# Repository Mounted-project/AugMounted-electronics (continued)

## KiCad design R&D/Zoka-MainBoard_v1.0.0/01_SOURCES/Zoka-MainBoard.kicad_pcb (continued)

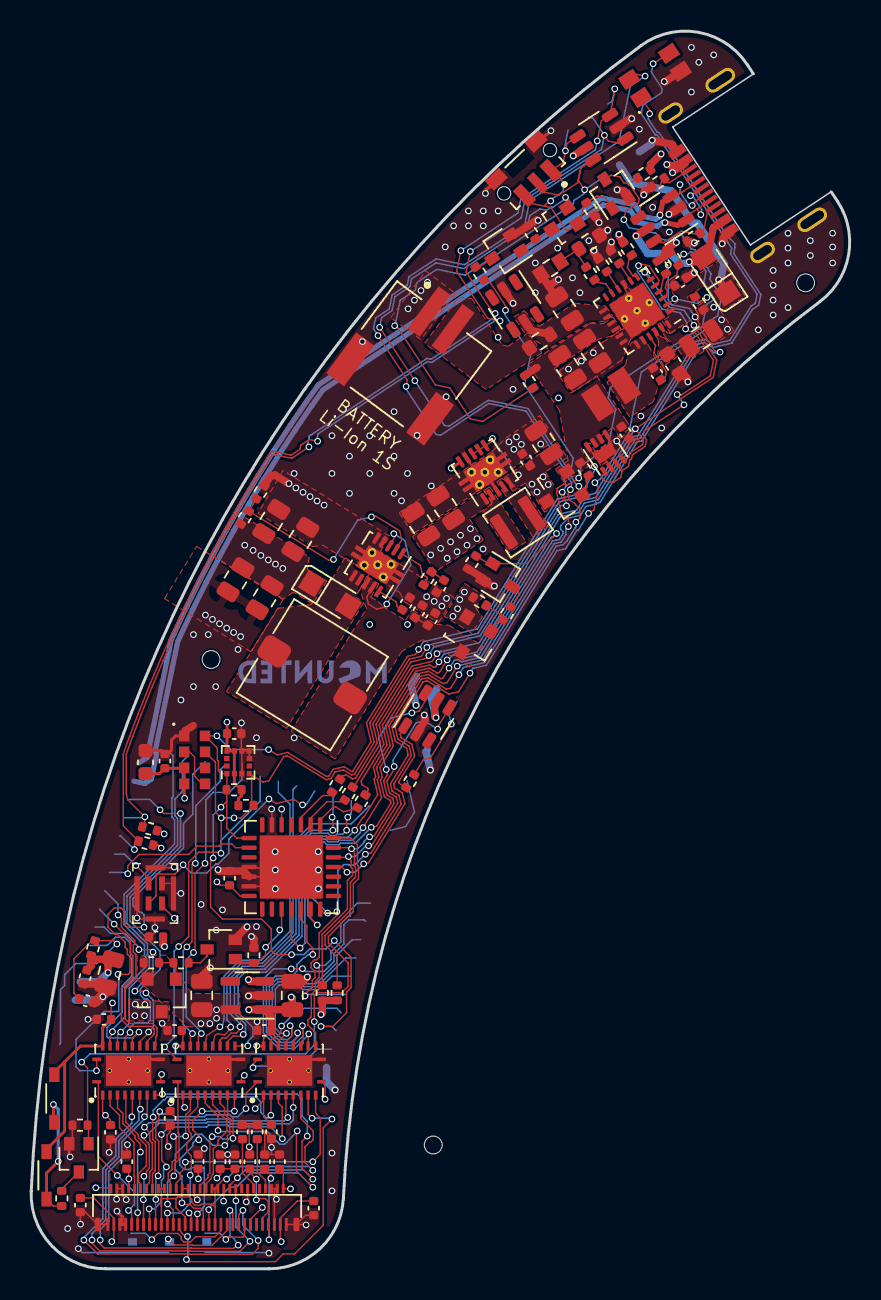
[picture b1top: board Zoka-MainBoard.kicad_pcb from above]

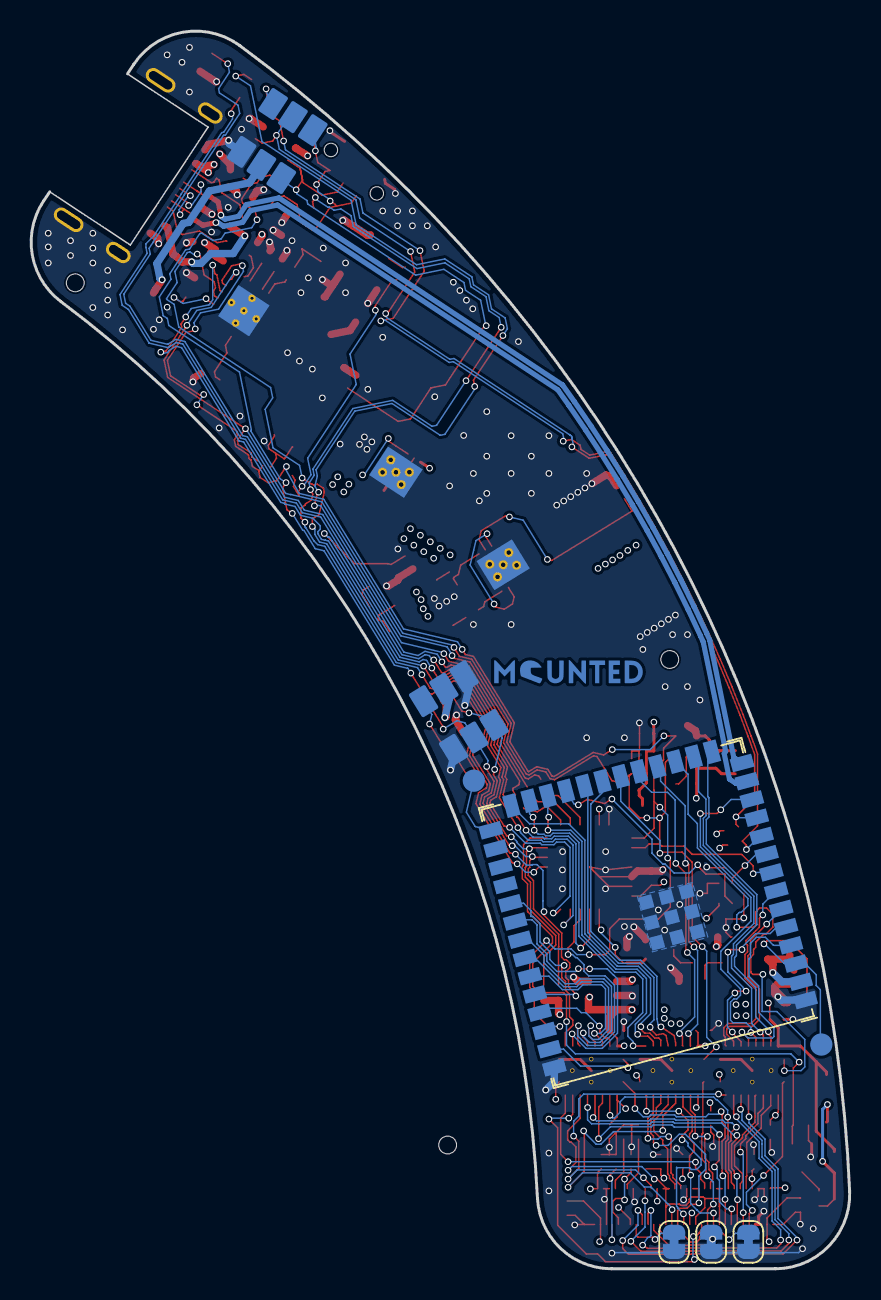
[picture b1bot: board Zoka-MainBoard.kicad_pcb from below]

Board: 4 copper layers, 55.1 x 83.3 mm, 136 parts (9 on the bottom side), 126 nets.

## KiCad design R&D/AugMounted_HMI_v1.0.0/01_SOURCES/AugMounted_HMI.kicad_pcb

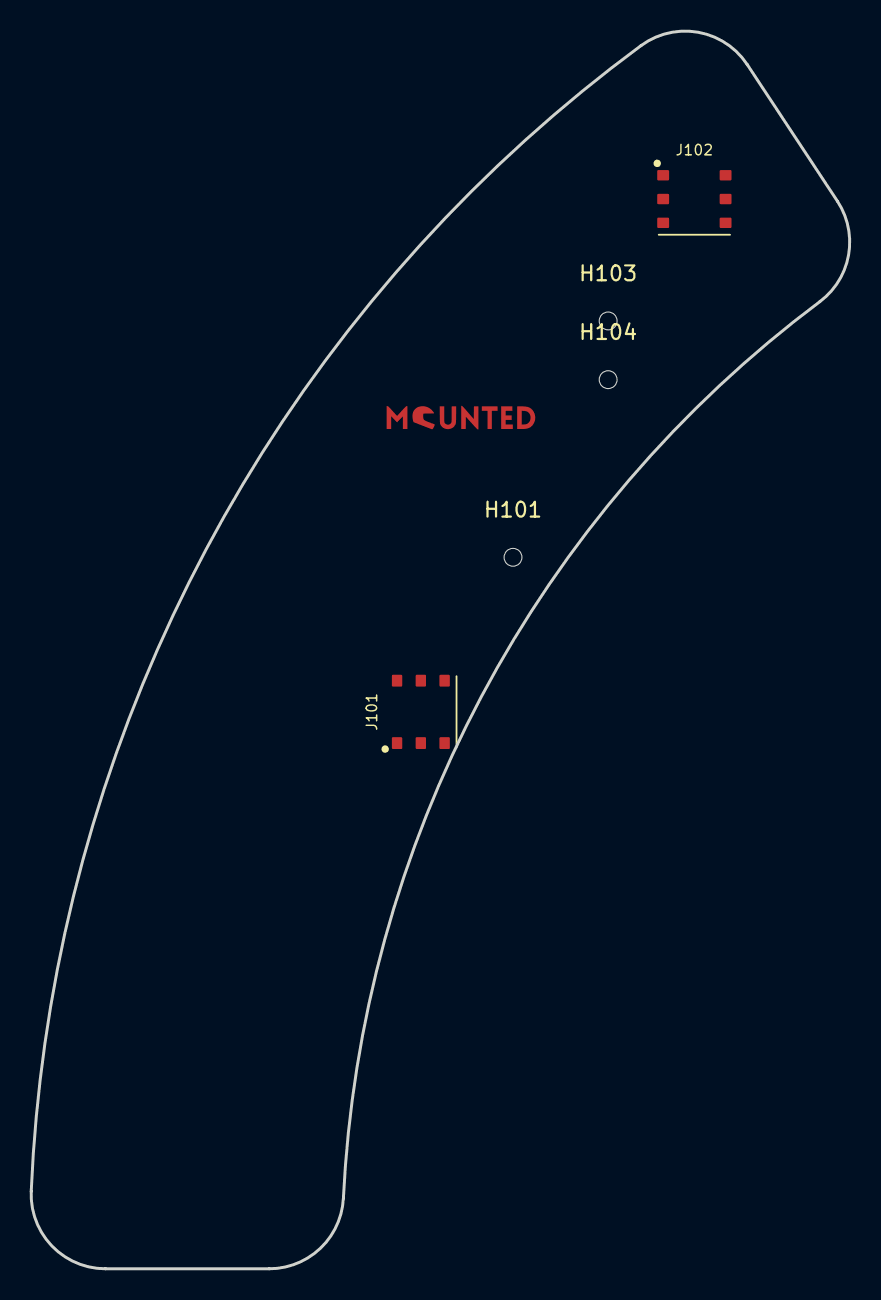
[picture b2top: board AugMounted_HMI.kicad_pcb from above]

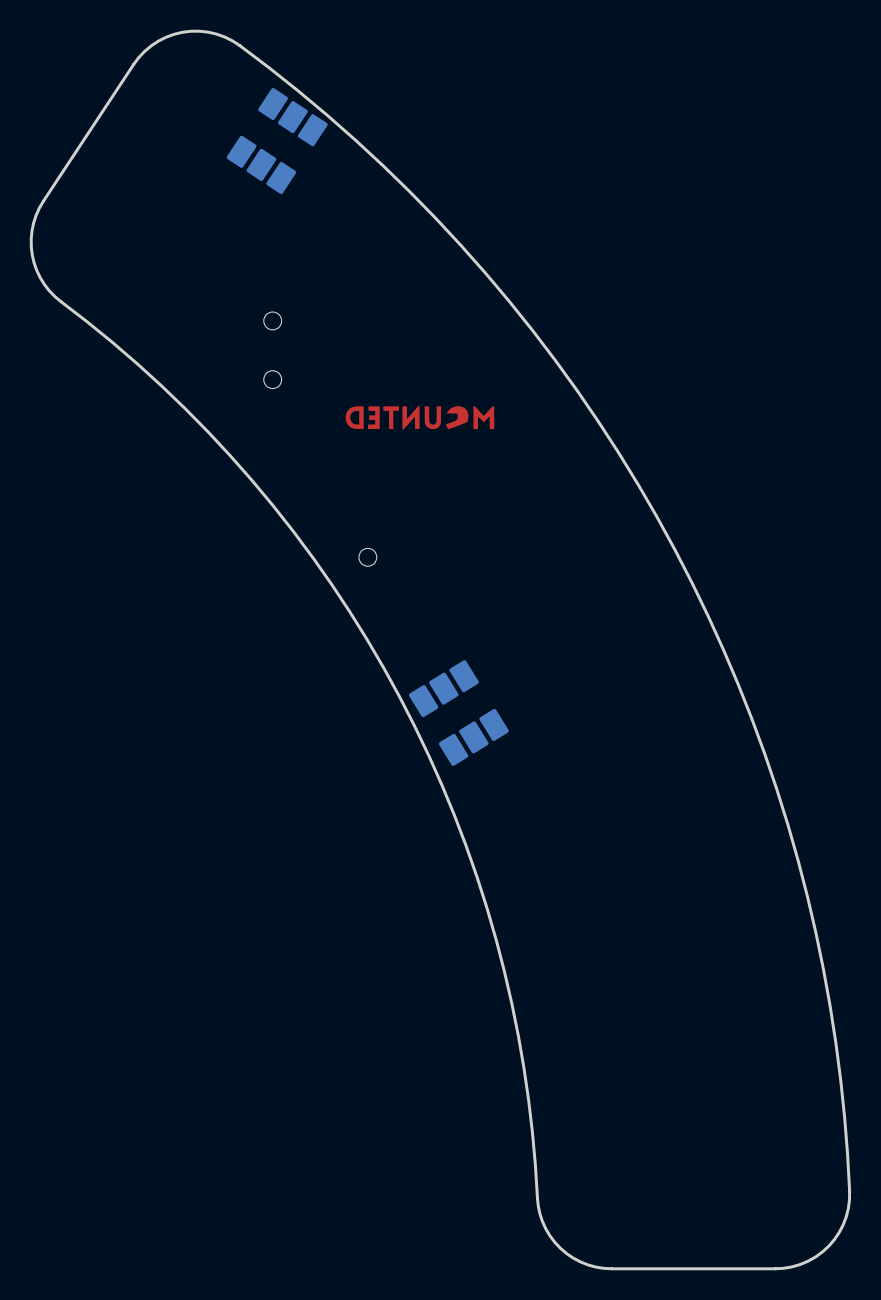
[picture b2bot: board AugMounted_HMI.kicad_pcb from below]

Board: 4 copper layers, 55.1 x 83.3 mm, 8 parts (2 on the bottom side), 3 nets, no tracks yet.

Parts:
H101, H103, H104: H_MOUNTING_HOLE_M1; MountingHole_1.2mm_M1
J101, J102: J_0788641001; J_788641001
J501, J504: J_0788641001_PAD; J_788641001_PAD
LOGO101: mounted_logo

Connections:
/GND_HMI_BOARD: J101.3, J102.3
GND: J501.3, J501.6, J504.3
unnamed: J101.1, J101.6

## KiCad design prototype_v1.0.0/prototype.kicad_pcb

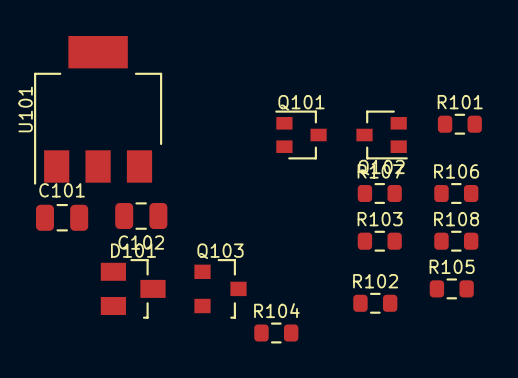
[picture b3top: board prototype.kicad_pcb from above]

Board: 2 copper layers, 15 parts (0 on the bottom side), 10 nets, no tracks yet.

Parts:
C101, C102: C_0805_4.7uF_16V_X7R_10%; C_0805_1608Metric
D101: D_MMBD1404; SOT-23_ONSEMI
Q101, Q102: Q_BSS123WQ-7-F; SOT-323_SC-70_DIODES_INC
Q103: Q_HSS2P10; SOT-23-3_DIODES_INCORPORATED
R101, R102, R103, R104, R105, R107, R108: R_0603_100k_1%_0.1W; R_0603_1608Metric
R106: R_0603_10k_1%_0.1W; R_0603_1608Metric
U101: U_AP2114HA-3.3TRG1; SOT-223-3_TABPIN2_DIODES_INC

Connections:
3.3V: C102.1, R101.2, U101.3 (VOUT)
/BATTERY_MEASURE: R107.2, R108.1
/BUTTON_PIN: Q101.3 (D), R101.1
BAT+: Q103.2 (S), R103.2, R105.1
GND: C101.2, C102.2, Q101.2 (S), Q102.2 (S), R102.2, R104.2, R108.2, U101.2 (GND)
unnamed: C101.1, Q103.3 (D), R107.1, U101.1 (VIN)
unnamed: D101.1 (A1), Q101.1 (G), R102.1
unnamed: D101.3 (K), Q102.1 (G), R104.1
unnamed: Q102.3 (D), R106.2
unnamed: Q103.1 (G), R105.2, R106.1

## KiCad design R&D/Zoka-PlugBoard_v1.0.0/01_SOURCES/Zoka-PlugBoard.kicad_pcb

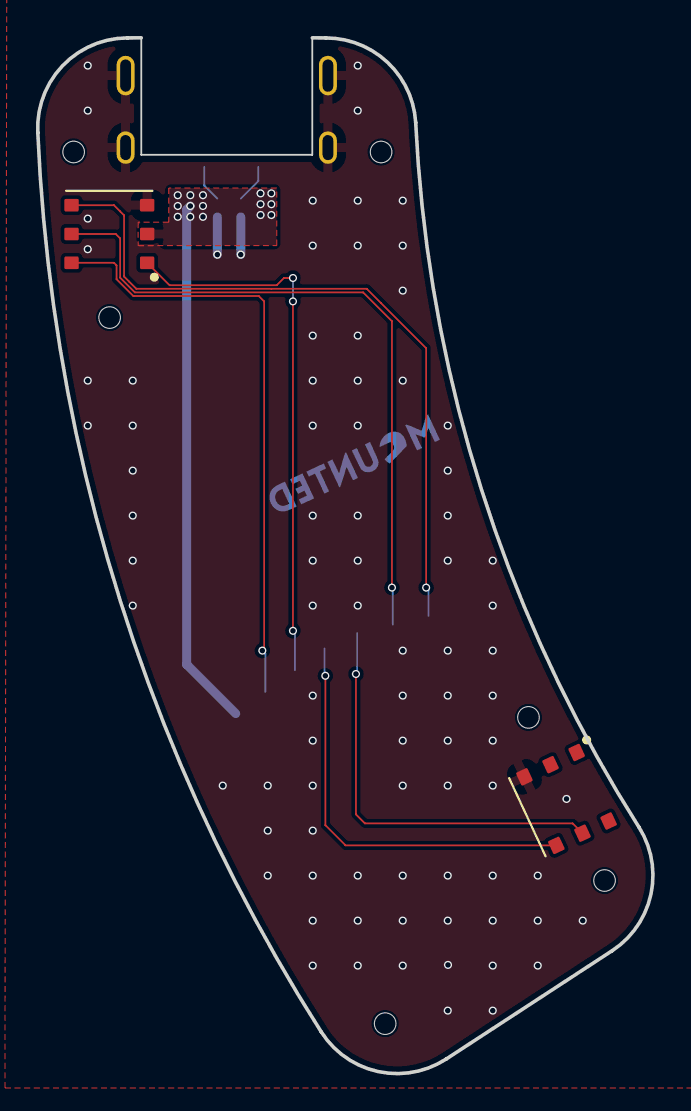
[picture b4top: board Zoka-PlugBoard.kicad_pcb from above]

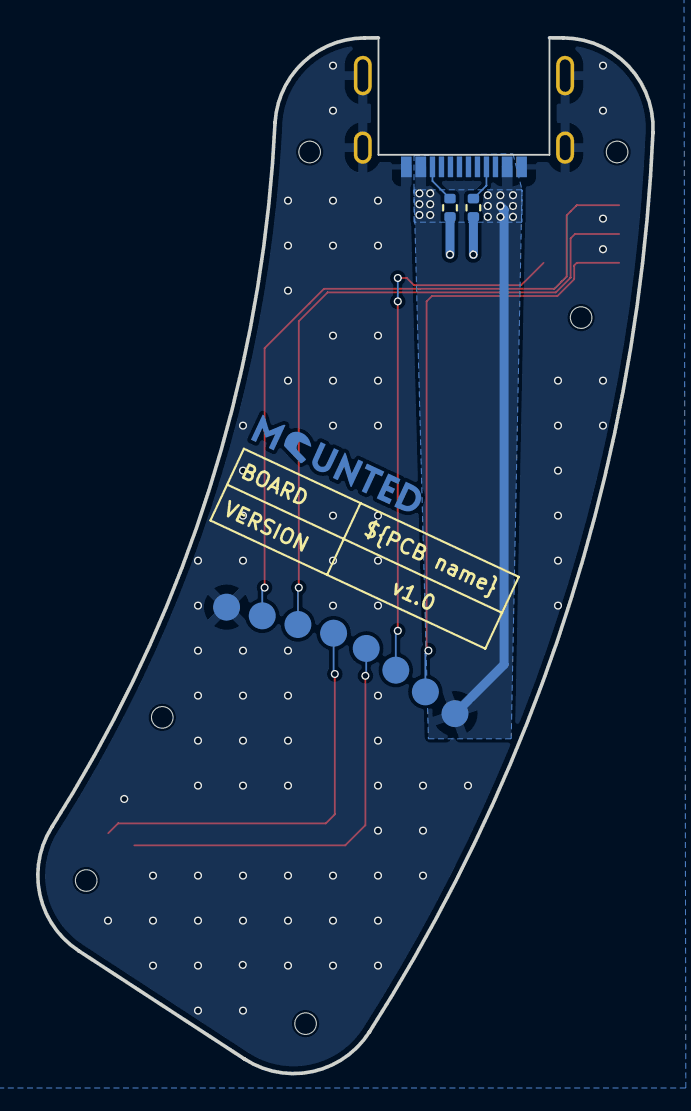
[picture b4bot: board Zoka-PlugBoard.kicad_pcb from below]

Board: 4 copper layers, 34.2 x 57.5 mm, 21 parts (13 on the bottom side), 11 nets.

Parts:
CART101: Cartouche_IO
H101, H102, H103, H104, H105, H108: H_MOUNTING_HOLE_M1; MountingHole_1.2mm_M1
J101, J102: J_0788641001; J_788641001
J103: J_TYPE-C-31-M-13
LOGO101: mounted_logo
R101, R102: R_0603_5.23k_1%_0.1W; R_0402_1005Metric
TP101, TP102, TP103, TP104, TP105, TP106, TP107, TP108: TESTPOINT_1.5MM

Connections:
/BUTTON1_HMI_BOARD: J101.5, TP106.1
/BUTTON2_HMI_BOARD: J101.4, TP105.1
/CC1: J103.A5 (CC1), R101.1
/CC2: J103.B5 (CC2), R102.1
/ENCODER_A_HMI_BOARD: J102.5, TP101.1
/ENCODER_B_HMI_BOARD: J102.4, TP102.1
/ENCODER_S1_HMI_BOARD: J102.1, TP103.1
/ENCODER_S2_HMI_BOARD: J102.6, TP104.1
GND: J101.3, J102.3, J103.A1 (GND), J103.A12 (GND), J103.B1 (GND), J103.B12 (GND), J103.GND, R101.2, R102.2, TP107.1
unnamed: J101.1, J101.6
VBUS: J102.2, J103.A4 (VBUS), J103.A9 (VBUS), J103.B4 (VBUS), J103.B9 (VBUS), TP108.1

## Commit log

2023-09-18 Added existing schematics of the prototype_v1.0.0
2023-11-05 started project
2023-11-05 Added Kicad project files
2023-11-05 Major components are done in library
2023-11-05 Created all components, placed them, and added images of typical applications. ECX334A and ESP32-S3 pdf are available in 00_RESOURCES
2023-11-08 Oled driving circuit done, need to connect everything to the ESP32
2023-11-15 Schematic 90% done
2023-11-15 Moved components
2023-11-16 Schematic done
2023-11-17 First revision of the layout
2023-11-23 Changed layout to a banana shape
2023-11-23 Added resistors for CC1 and CC2 pins, layout is started on the high part of the board
2023-11-24 Changed layout + all passive to 0402
2023-11-28 Component layout is done, routing video signals is done too.
2023-12-08 Layout almost done
2023-12-08 Layout done
2023-12-13 Excluded violations, added via stiching for GND. Ready for review/Production
2023-12-13 Stated receptacle board, need to change the name from HMI to receptacle
2023-12-13 Library changes
2024-01-17 Pushing all boards
